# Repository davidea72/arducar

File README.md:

# arducar
arduino based car with mpu 6050 gyro

l' intento è quello di realizzare una macchinina comandata da un app sul telefono android 

 la macchinina deve andare avanti e indietro , destra e sinistra , deve fermarsi in automatico dopo un po che non riceve comandi 
 
 siccome non si trovano due motori che girino alla stessa velocità la macchinina tende sempre a sterzare da un lato, per correggere questo comportamento si è inserito il giroscopio GY-521 basato sull' mpu 6050
 
 il giroscopio puo' esser utilizzato in modalità normale , o con l' ausilio della DMP interna , in tal caso  va utilizzato il pin dell' interrupt per segnalare ad arduino quando la dmp ha finito i calcoli e i dati sono pronti da leggere 
 
 Anche in tale configurazione ho riscontrato che i primi 20 secondi circa la lettura non è stabile , quindi bisogna aspettare circa 20 secondi affinchè la lettura si stabilizzi (con un errore inferiore a 0.05 gradi) 
 
 ogni volta che la macchinina si ferma viene calcolato un nuovo offset in modo da considerare sempre come rotta 0 gradi la direzione che ha qualche istante prima della partenza 
 
 Per far andare dritta la macchinina quindi , viene passato al PID la rotta attuale , quella voluta (come setpoint) e se ne ottiene il valore da passare ai motori come correzione (output), questo valore è calcolato in base ai 3 parametri Kp , Ki e Kd 
 
 infine viene effettuata una lettura della batteria , tale tensione è ricavata tramite un partitore resistivo da quella di alimentazione dai supercondensatori , la lettura è riparametrizzata tra due valori che corrispondono a 7V - 0% e 11,7V 100% 
 l' app sul telefonino è stata creata tramite appinventor , del quale ho apprezzato la facilità d' uso ma ho anche trovato uno dei suoi limiti , non è possibile processare un grosso flusso dati dalla macchinina verso il telefonino , se mando tutti i dati di debug  sull' app vanno accumulando ritardo, arrivando ad una decina di secondi di ritardo fino a bloccare a volte l' app 
 
 Per debuggare sono stato costretto ad utilizzare il portatile collegato in bluetooth alla macchinina con un emulatore terminale quale minicom. 
 per facilitare il debug , le varie parti di debug sono attivabili e disattivabili a runtime , cosi' come anche i parametri K del pid sono modificabili a runtime con step di 0.5 

 Il file Giulia.aia è il progetto da importare su app inventor per creare e/o modificare l' app android creata da Giulia

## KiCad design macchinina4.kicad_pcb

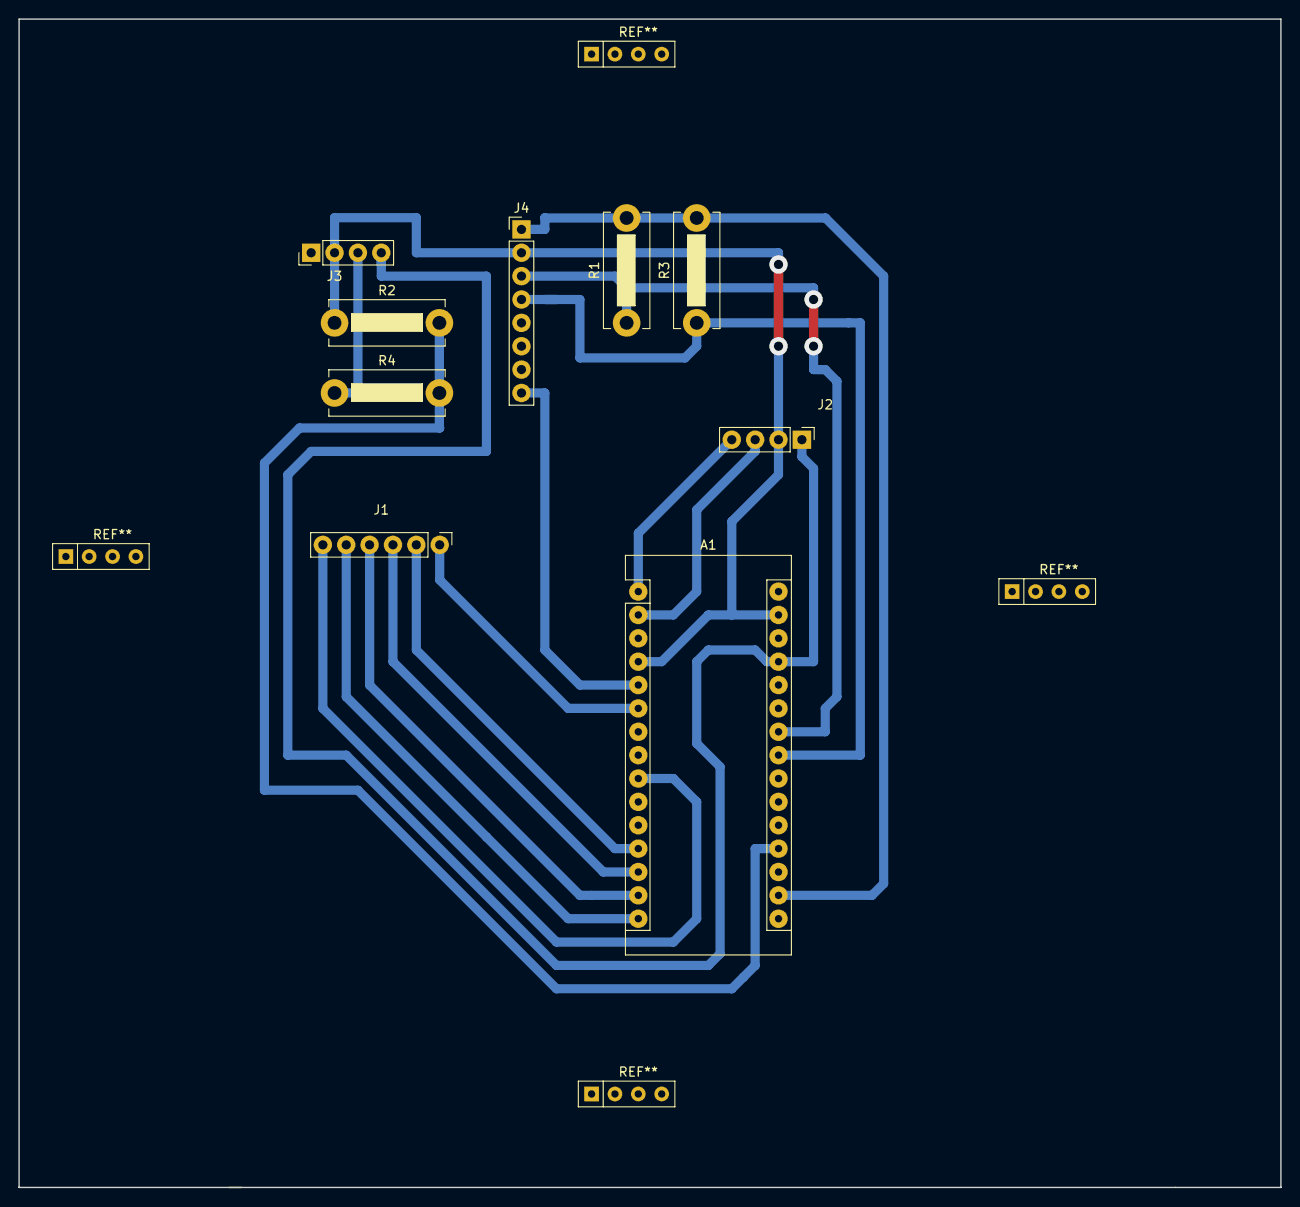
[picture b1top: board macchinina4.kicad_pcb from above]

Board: 2 copper layers, 137.2 x 127.0 mm, 9 parts (0 on the bottom side), 16 nets.

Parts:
A1: Arduino_Nano_v3.x; Arduino_Nano
J1: L298N; PinHeader_1x06_P2.54mm_Vertical
J2: HC-06; PinHeader_1x04_P2.54mm_Vertical
J3: ALIM; PinHeader_1x04_P2.54mm_Vertical
J4: GY-521; PinHeader_1x08_P2.54mm_Vertical
R1, R2, R3, R4: R; R_Bare_Metal_Element_L12.4mm_W4.8mm_P11.40mm

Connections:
/+5V: A1.27, J2.1, J3.4
/EN0: A1.9, J1.6
/EN1: A1.6, J1.1
/GND: A1.4, A1.29, J2.2, J3.2, J4.2, R2.1
/IN1: A1.12, J1.2
/IN2: A1.13, J1.3
/IN3: A1.14, J1.4
/IN4: A1.15, J1.5
/TX: A1.2, J2.3
unnamed: A1.1, J2.4
unnamed: A1.5, J4.8
unnamed: A1.17, J4.1, R1.2, R3.2
unnamed: A1.19, R2.2, R4.2
unnamed: A1.23, J4.4, R3.1
unnamed: A1.24, J4.3, R1.1
unnamed: J3.3, R4.1

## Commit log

2020-02-20 schema elettrico kicad
2020-02-20 pcb kicad
2020-02-20 disposizione componenti
2020-02-20 stampato rame
2020-02-20 schema elettrico
